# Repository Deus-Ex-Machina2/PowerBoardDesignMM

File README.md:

# Mircomouse Power Board Design
### Produced by: Rafael Cardoso and Amir Dollie 

This repository serves to hold and offer version control for the mircomouse power board designed.

**IMPORTANT:** since KiCAD, which was used to produce the necessary production files for submission to JLCPCB, does not allow easy merging capabilities for simultaneous development the following file strcuture was used:<br><br>

- Final Project Workfolder contains the final submission schematic and PCB: Final Project Workfolder -> Final
        (The other files in this section are for previous revision submissions and also contain images of JLCPCB quotes...etc)
- Raf'sWorkspace/MMPOwerBoardKiCAD9Version contains the most recent (current) schematic and pcb file for the entire PCB board.
- SchematicLibrary contains the files of all custom and imported symbols and footprints associated with the design.

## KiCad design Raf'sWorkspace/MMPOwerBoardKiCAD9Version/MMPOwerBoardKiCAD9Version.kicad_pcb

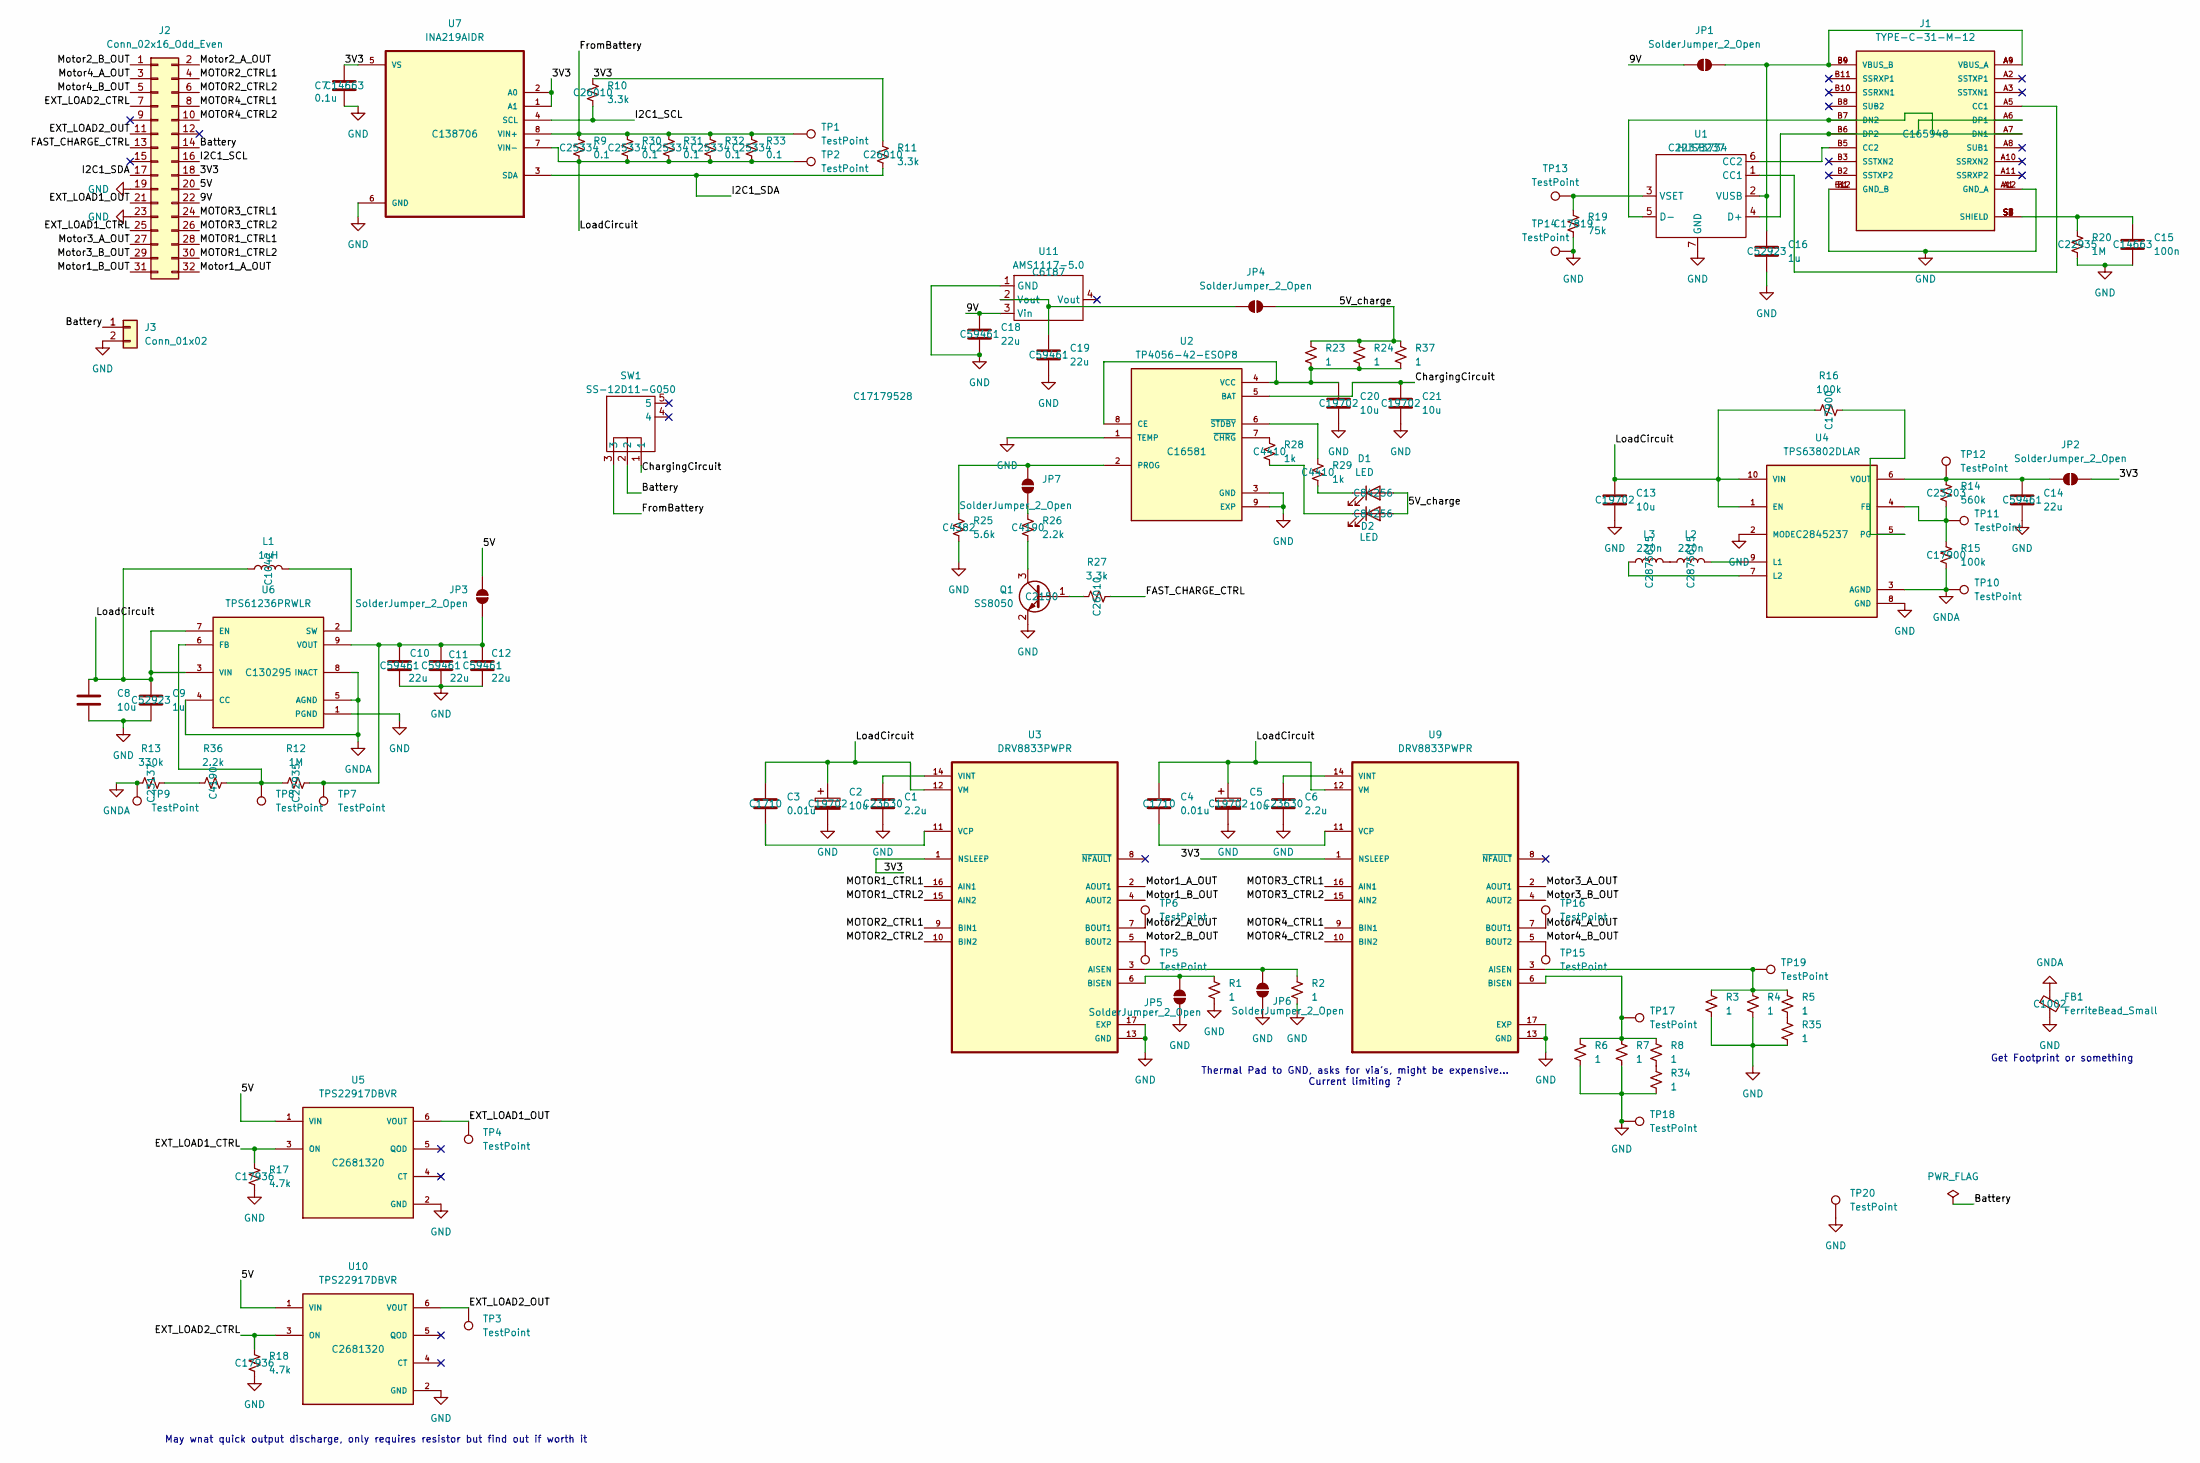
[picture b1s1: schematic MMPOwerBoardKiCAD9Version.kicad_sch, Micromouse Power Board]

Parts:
C1, C6: 2.2u; C_0603_1608Metric; LCSC C23630
C2, C5, C8, C13, C20, C21: 10u; C_0603_1608Metric; LCSC C19702
C3, C4: 0.01u; C_0805_2012Metric; LCSC C1710
C7: 0.1u; C_0603_1608Metric; LCSC C14663
C9, C16: 1u; C_0402_1005Metric; LCSC C52923
C10, C11, C12, C14, C18, C19: 22u; C_0603_1608Metric; LCSC C59461
C15: 100n; C_0603_1608Metric; LCSC C14663
D1, D2: LED; LED_0805_2012Metric; LCSC C84256
FB1: FerriteBead_Small; L0603; LCSC C1002
J1: TYPE-C-31-M-12; USB-C_SMD-TYPE-C-31-M-12; PARTREV A; LCSC C165948
J2: Conn_02x16_Odd_Even; PinHeader_2x16_P2.54mm_Vertical
J3: Conn_01x02; JST_PH_B2B-PH-K_1x02_P2.00mm_Vertical
JP1, JP2, JP3, JP4, JP5, JP6, JP7: SolderJumper_2_Open; SolderJumper-2_P1.3mm_Open_Pad1.0x1.5mm
L1: 1uH; L_0805_2012Metric; LCSC C1042
L2, L3: 220n; IND-SMD_L4.5-W4.1_TMPA0402SP; LCSC C2875615
Q1: SS8050; SOT-23; LCSC C2150
R1, R2, R3, R4, R5, R6, R7, R8, R23, R24, R34, R35, R37: 1; R_1206_3216Metric; LCSC C17928
R9, R30, R31, R32, R33: 0.1; R_1206_3216Metric; LCSC C25334
R10, R11: 3.3k; R_0805_2012Metric; LCSC C26010
R12, R20: 1M; R_0603_1608Metric; LCSC C22935
R13: 330k; R_0603_1608Metric_Pad0.98x0.95mm_HandSolder; LCSC C23137
R14: 560k; R_0603_1608Metric_Pad0.98x0.95mm_HandSolder; LCSC C23203
R15, R16: 100k; R_1206_3216Metric; LCSC C17900
R17, R18: 4.7k; R_1206_3216Metric; LCSC C17936
R19: 75k; R_0805_2012Metric_Pad1.20x1.40mm_HandSolder; LCSC C17819
R25: 5.6k; R_0805_2012Metric; LCSC C4382
R26: 2.2k; R_0603_1608Metric_Pad0.98x0.95mm_HandSolder; LCSC C4190
R27: 3.3k; R_0805_2012Metric_Pad1.20x1.40mm_HandSolder; LCSC C26010
R28, R29: 1k; R_1206_3216Metric; LCSC C4410
R36: 2.2k; R_0603_1608Metric; LCSC C4190
SW1: SS-12D11-G050; LCSC C17179528
TP1, TP2, TP3, TP4, TP5, TP6, TP7, TP8, TP9, TP10, TP11, TP12, TP13, TP14, TP15, TP16, TP17, TP18, TP19: TestPoint; TestPoint_Pad_1.5x1.5mm
TP20: TestPoint; TestPoint_Pad_4.0x4.0mm
U1: HUSB237; HUSB237-AA001DN06R-; LCSC C22373734
U2: TP4056-42-ESOP8; SOIC127P600X175-9N; PARTREV NA; LCSC C16581
U3, U9: DRV8833PWPR; HTSSOP-16-1EP_4.4x5mm_P0.65mm_EP3.4x5mm; PARTREV E; LCSC C50506
U4: TPS63802DLAR; VREG_TPS63802DLAR; PARTREV B; LCSC C2845237
U5, U10: TPS22917DBVR; SOT95P280X145-6N; PARTREV B; LCSC C2681320
U6: TPS61236PRWLR; CONV_TPS61235PRWLR; LCSC C130295
U7: INA219AIDR; SOIC127P599X175-8N; LCSC C138706
U11: AMS1117-5.0; SOT-223_L6.5-W3.5-P2.30-LS7.0-BR; LCSC C6187

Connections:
/3V3: C7.1, J2.18, JP2.2 (B), R10.1, R11.1, U3.1 (NSLEEP), U7.1 (A1), U7.2 (A0), U7.5 (VS), U9.1 (NSLEEP)
/5V: J2.20, JP3.1 (A), U5.1 (VIN), U10.1 (VIN)
/5V_charge: D1.2 (A), D2.2 (A), JP4.2 (B), R23.1, R24.1, R37.1
/9V: C18.1, J2.22, JP1.1 (A), U11.3 (Vin)
/Battery: J2.14, J3.1, SW1.2
/ChargingCircuit: C21.1, SW1.1, U2.5 (BAT)
/EXT_LOAD1_CTRL: J2.25, R17.1, U5.3 (ON)
/EXT_LOAD1_OUT: J2.21, TP4.1, U5.6 (VOUT)
/EXT_LOAD2_CTRL: J2.7, R18.1, U10.3 (ON)
/EXT_LOAD2_OUT: J2.11, TP3.1, U10.6 (VOUT)
/FAST_CHARGE_CTRL: J2.13, R27.1
/FromBattery: R9.1, R30.1, R31.1, R32.1, R33.1, SW1.3, TP1.1, U7.8 (VIN+)
/I2C1_SCL: J2.16, R10.2, U7.4 (SCL)
/I2C1_SDA: J2.17, R11.2, U7.3 (SDA)
/LoadCircuit: C2.1, C3.1, C4.1, C5.1, C8.1, C9.1, C13.1, L1.1, R9.2, R16.1, R30.2, R31.2, R32.2, R33.2, TP2.1, U3.12 (VM), U4.1 (EN), U4.10 (VIN), U6.3 (VIN), U6.7 (EN), U7.7 (VIN-), U9.12 (VM)
/MOTOR1_CTRL1: J2.28, U3.16 (AIN1)
/MOTOR1_CTRL2: J2.30, U3.15 (AIN2)
/MOTOR2_CTRL1: J2.4, U3.9 (BIN1)
/MOTOR2_CTRL2: J2.6, U3.10 (BIN2)
/MOTOR3_CTRL1: J2.24, U9.16 (AIN1)
/MOTOR3_CTRL2: J2.26, U9.15 (AIN2)
/MOTOR4_CTRL1: J2.8, U9.9 (BIN1)
/MOTOR4_CTRL2: J2.10, U9.10 (BIN2)
/Motor1_A_OUT: J2.32, U3.2 (AOUT1)
/Motor1_B_OUT: J2.31, U3.4 (AOUT2)
/Motor2_A_OUT: J2.2, TP6.1, U3.7 (BOUT1)
/Motor2_B_OUT: J2.1, TP5.1, U3.5 (BOUT2)
/Motor3_A_OUT: J2.27, U9.2 (AOUT1)
/Motor3_B_OUT: J2.29, U9.4 (AOUT2)
/Motor4_A_OUT: J2.3, TP16.1, U9.7 (BOUT1)
/Motor4_B_OUT: J2.5, TP15.1, U9.5 (BOUT2)
GND: C1.2, C2.2, C5.2, C6.2, C7.2, C8.2, C9.2, C10.2, C11.2, C12.2, C13.2, C14.2, C15.2, C16.2, C18.2, C19.2, C20.2, C21.2, FB1.2, J1.A1 (GND_A), J1.A12 (GND_A), J1.B1 (GND_B), J1.B12 (GND_B), J2.19, J2.23, J3.2, JP5.2 (B), JP6.2 (B), Q1.2 (E), R1.2, R2.2, R3.2, R4.2, R6.2, R7.2, R17.2, R18.2, R19.2, R20.2, R25.1, R34.2, R35.2, TP14.1, TP18.1, TP20.1, U1.7 (GND), U2.1 (TEMP), U2.3 (GND), U2.9 (EXP), U3.13 (GND), U3.17 (EXP), U4.2 (MODE), U4.8 (GND), U5.2 (GND), U6.1 (PGND), U7.6 (GND), U9.13 (GND), U9.17 (EXP), U10.2 (GND), U11.1 (GND)
GNDA: FB1.1, R13.1, R15.2, TP9.1, TP10.1, U4.3 (AGND), U6.4 (CC), U6.5 (AGND), U6.8 (INACT)
unnamed: C15.1, J1.S1 (SHIELD), J1.S2 (SHIELD), J1.S3 (SHIELD), J1.S4 (SHIELD), J1.S5 (SHIELD), J1.S6 (SHIELD), J1.S7 (SHIELD), J1.S8 (SHIELD), R20.1
unnamed: D1.1 (K), R29.1
unnamed: D2.1 (K), R28.1
unnamed: J1.A5 (CC1), U1.1 (CC1)
unnamed: J1.B5 (CC2), U1.6 (CC2)
unnamed: J1.A7 (DN1), J1.B7 (DN2), U1.5 (D-)
unnamed: J1.A6 (DP1), J1.B6 (DP2), U1.4 (D+)
unnamed: C16.1, J1.A4 (VBUS_A), J1.A9 (VBUS_A), J1.B4 (VBUS_B), J1.B9 (VBUS_B), JP1.2 (B), U1.2 (VUSB)
unnamed: C14.1, JP2.1 (A), R14.1, TP12.1, U4.6 (VOUT)
unnamed: C10.1, C11.1, C12.1, JP3.2 (B), R12.2, TP7.1, U6.9 (VOUT)
unnamed: C19.1, JP4.1 (A), U11.2 (Vout)
unnamed: JP5.1 (A), R1.1, U3.6 (BISEN)
unnamed: JP6.1 (A), R2.1, U3.3 (AISEN)
unnamed: JP7.1 (A), R26.2
unnamed: JP7.2 (B), R25.2, U2.2 (PROG)
unnamed: L2.1, L3.2
unnamed: Q1.1 (B), R27.2
unnamed: Q1.3 (C), R26.1
unnamed: R13.2, R36.1
unnamed: R8.2, R34.1
unnamed: R5.2, R35.1
unnamed: R19.1, TP13.1, U1.3 (VSET)
unnamed: C20.1, R23.2, R24.2, R37.2, U2.4 (VCC), U2.8 (CE)
unnamed: R28.2, U2.7 (~CHRG)
unnamed: R29.2, U2.6 (~STDBY)
unnamed: C3.2, U3.11 (VCP)
unnamed: C1.1, U3.14 (VINT)
unnamed: R14.2, R15.1, TP11.1, U4.4 (FB)
unnamed: L2.2, U4.9 (L1)
unnamed: L3.1, U4.7 (L2)
unnamed: R16.2, U4.5 (PG)
unnamed: R12.1, R36.2, TP8.1, U6.6 (FB)
unnamed: L1.2, U6.2 (SW)
unnamed: R3.1, R4.1, R5.1, TP19.1, U9.3 (AISEN)
unnamed: R6.1, R7.1, R8.1, TP17.1, U9.6 (BISEN)
unnamed: C4.2, U9.11 (VCP)
unnamed: C6.1, U9.14 (VINT)

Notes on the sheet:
Get Footprint or something
Thermal Pad to GND, asks for via's, might be expensive... Current limiting ?
May wnat quick output discharge, only requires resistor but find out if worth it

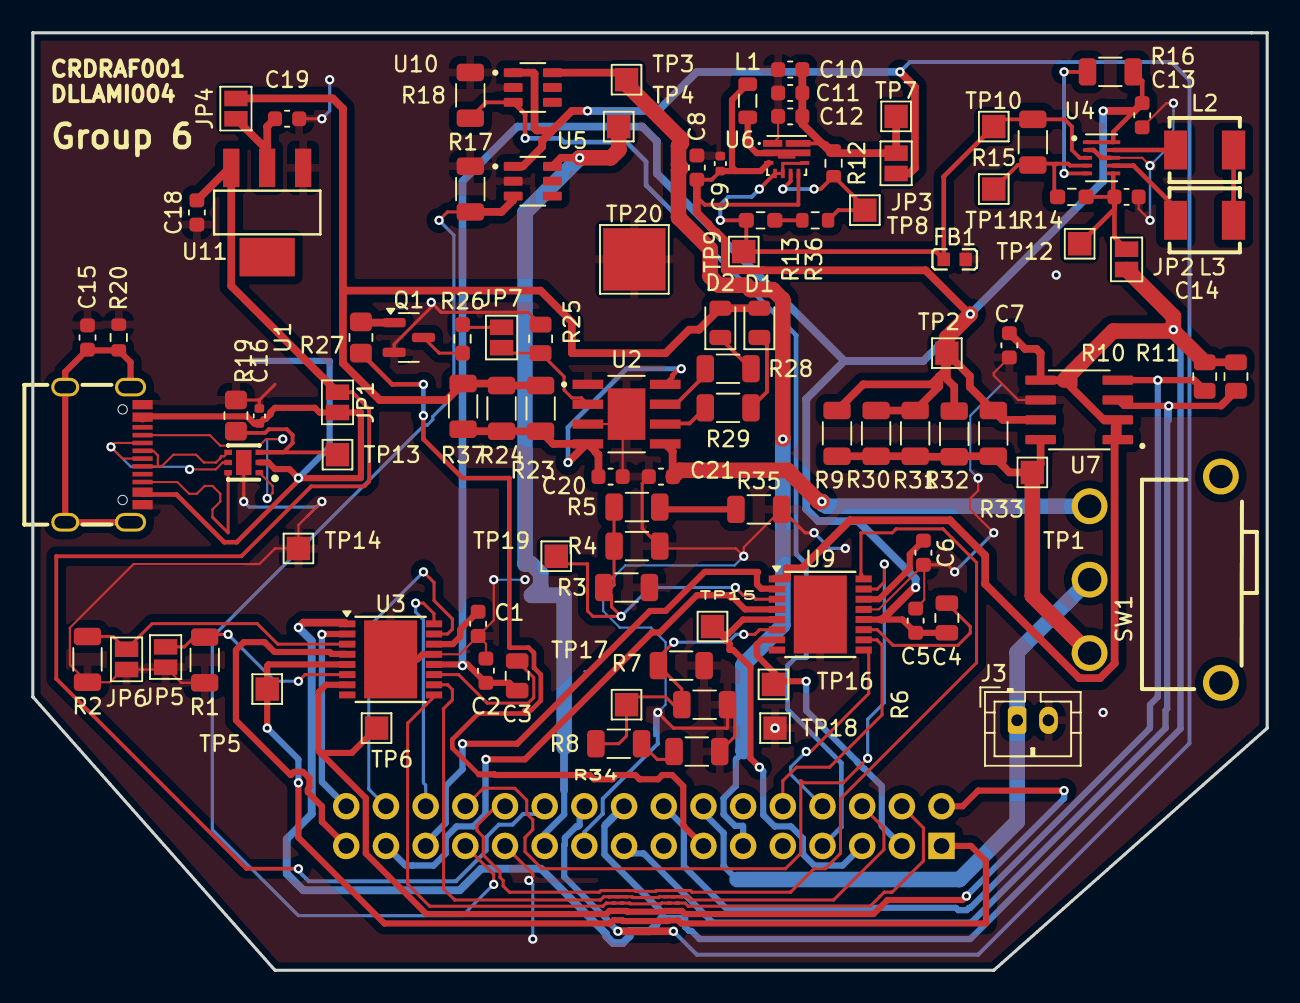
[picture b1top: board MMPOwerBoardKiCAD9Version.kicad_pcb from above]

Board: 2 copper layers, 79.0 x 60.0 mm, 103 parts (1 on the bottom side), 70 nets.

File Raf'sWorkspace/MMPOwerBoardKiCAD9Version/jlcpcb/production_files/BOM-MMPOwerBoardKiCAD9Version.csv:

Comment,Designator,Footprint,LCSC,Quantity
FerriteBead_Small,FB1,L0603,C1002,1
1uH,L1,L_0805_2012Metric,C1042,1
TPS61236PRWLR,U6,CONV_TPS61235PRWLR,C130295,1
INA219AIDR,U7,SOIC127P599X175-8N,C138706,1
100n,"C15,C7",C_0603_1608Metric,C14663,2
TP4056-42-ESOP8,U2,SOIC127P600X175-9N,C16581,1
TYPE-C-31-M-12,J1,USB-C_SMD-TYPE-C-31-M-12,C165948,1
0.01u,"C3,C4",C_0805_2012Metric,C1710,2
SS-12D11-G050,SW1,SS-12D11-G050,C17179528,1
75k,R19,R_0805_2012Metric_Pad1.20x1.40mm_HandSolder,C17819,1
100k,"R15,R16",R_1206_3216Metric,C17900,2
1,"R1,R2,R23,R24,R3,R34,R35,R37,R4,R5,R6,R7,R8",R_1206_3216Metric,C17928,13
4.7k,"R17,R18",R_1206_3216Metric,C17936,2
10u,"C13,C2,C20,C21,C5,C8",C_0603_1608Metric,C19702,6
SS8050,Q1,SOT-23,C2150,1
HUSB237,U1,HUSB237-AA001DN06R-,C22373734,1
1M,"R12,R20",R_0603_1608Metric,C22935,2
330k,R13,R_0603_1608Metric_Pad0.98x0.95mm_HandSolder,C23137,1
560k,R14,R_0603_1608Metric_Pad0.98x0.95mm_HandSolder,C23203,1
2.2u,"C1,C6",C_0603_1608Metric,C23630,2
0.1,"R30,R31,R32,R33,R9",R_1206_3216Metric,C25334,5
3.3k,"R10,R11,R27",R_0805_2012Metric,C26010,3
TPS22917DBVR,"U10,U5",SOT95P280X145-6N,C2681320,2
TPS63802DLAR,U4,VREG_TPS63802DLAR,C2845237,1
220n,"L2,L3",IND-SMD_L4.5-W4.1_TMPA0402SP,C2875615,2
2.2k,"R26,R36",R_0603_1608Metric_Pad0.98x0.95mm_HandSolder,C4190,2
5.6k,R25,R_0805_2012Metric,C4382,1
1k,"R28,R29",R_1206_3216Metric,C4410,2
DRV8833PWPR,"U3,U9",HTSSOP-16-1EP_4.4x5mm_P0.65mm_EP3.4x5mm,C50506,2
1u,"C16,C9",C_0402_1005Metric,C52923,2
22u,"C10,C11,C12,C14,C18,C19",C_0603_1608Metric,C59461,6
AMS1117-5.0,U11,SOT-223_L6.5-W3.5-P2.30-LS7.0-BR,C6187,1
LED,"D1,D2",LED_0805_2012Metric,C84256,2
TestPoint,TP20,TestPoint_Pad_4.0x4.0mm,,1

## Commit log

2025-03-25 Added Librarby for most chosen components footprint and schematics
2025-03-25 Added to library and updated schematic in Raf Work folder
2025-03-26 Added a few things to schematic and added new LDO schematic to library
2025-03-26 Almost complete schematic
2025-03-27 Final Schematic complete with test points and jumpers
2025-03-27 Added BOM and PCB and LCSC numbers, Schematic complete
2025-03-27 Organised PCB on recommended board size
2025-03-27 Added wiring of the PCB with Free-router
2025-03-27 Revert "Added wiring of the PCB with Free-router"
    This reverts commit c34e8a51645d4334bd9fe00579e44e527089207a.
2025-03-27 Added all tracks
2025-03-27 PCB seems to be done - BOM also generated
2025-03-27 GTFO Finished
2025-03-28 A few minor changes to improve results on rule checker: 0,1mm adjusted to 0,15mm, regions of silkscreen on pad were removed
2025-03-28 Added Drill hole space x1 to hold up board
2025-04-09 Made changes to hole sizes, minimum track width stuff (1.5mm) and other compliance things
2025-04-09 Changed the USB-C connector, and connected it - removed Ground layers, changed silkscreens for a few units
2025-04-09 Fixed PCB board, DRC has 0 errors now apparently
2025-04-09 Added the JLC PCB submission pcis and stuff [named incorrectedly
2025-04-09 Final files for resubmit attached in Final Workspace-> Final
